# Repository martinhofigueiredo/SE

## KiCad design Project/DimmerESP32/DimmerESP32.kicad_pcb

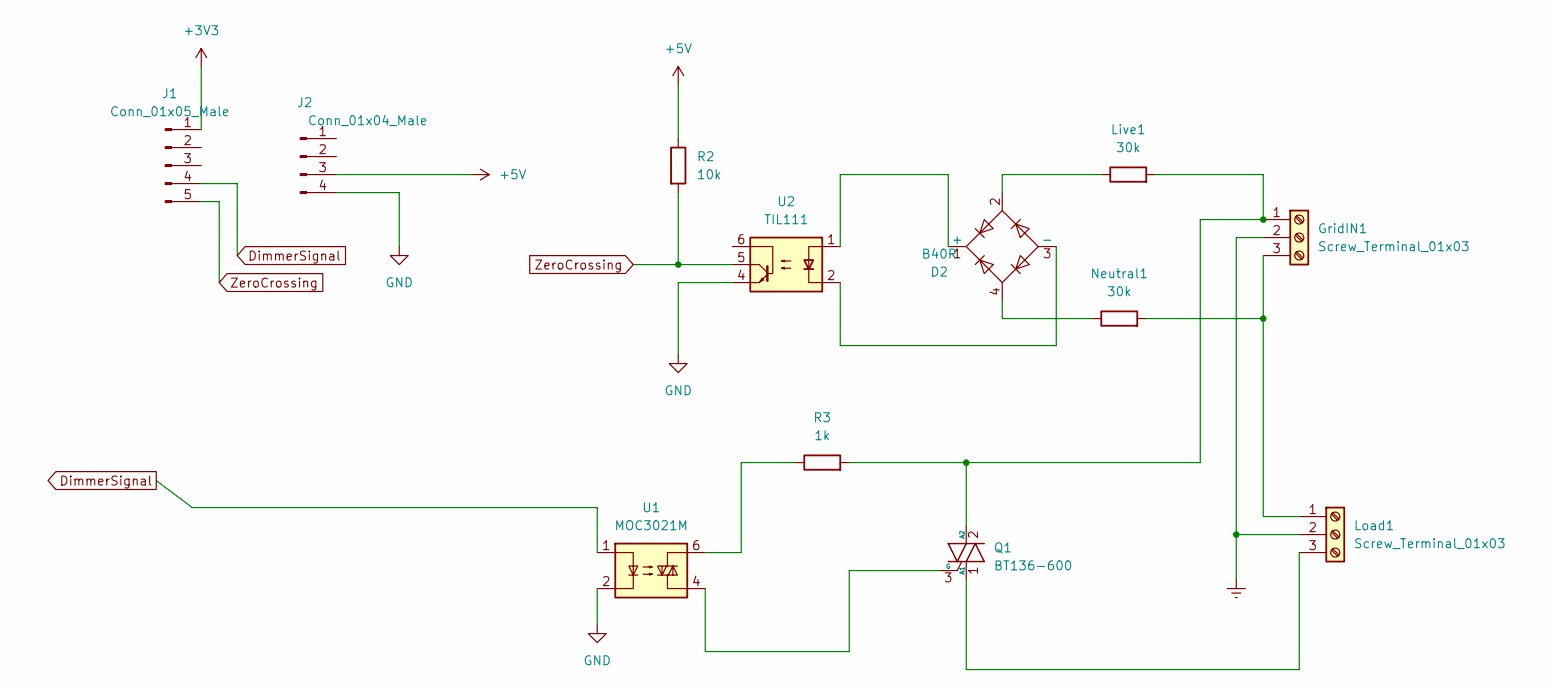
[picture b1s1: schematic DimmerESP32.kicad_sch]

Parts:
D2: B40R; Diode_Bridge_Round_D9.0mm
GridIN1: Screw_Terminal_01x03; TerminalBlock_Altech_AK300-3_P5.00mm
J1: Conn_01x05_Male; PinHeader_1x05_P2.54mm_Vertical
J2: Conn_01x04_Male; PinHeader_1x04_P2.54mm_Vertical
Live1: 30k; R_Axial_DIN0207_L6.3mm_D2.5mm_P10.16mm_Horizontal
Load1: Screw_Terminal_01x03; TerminalBlock_Altech_AK300-3_P5.00mm
Neutral1: 30k; R_Axial_DIN0207_L6.3mm_D2.5mm_P10.16mm_Horizontal
Q1: BT136-600; TO-220-3_Vertical
R2: 10k; R_Axial_DIN0207_L6.3mm_D2.5mm_P10.16mm_Horizontal
R3: 1k; R_Axial_DIN0207_L6.3mm_D2.5mm_P10.16mm_Horizontal
U1: MOC3021M; DIP-5-6_W7.62mm
U2: TIL111; DIP-6_W7.62mm

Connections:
+3V3: J1.1
+5V: J2.3, R2.1
DimmerSignal: J1.4, U1.1
Earth: GridIN1.2, Load1.2
GND: J2.4, U1.2, U2.4
unnamed: D2.1 (+), U2.1
unnamed: D2.2, Live1.1
unnamed: D2.3 (-), U2.2
unnamed: D2.4, Neutral1.1
unnamed: GridIN1.1, Live1.2, Q1.2 (A2), R3.2
unnamed: GridIN1.3, Load1.1, Neutral1.2
unnamed: Load1.3, Q1.1 (A1)
unnamed: Q1.3 (G), U1.4
unnamed: R3.1, U1.6
ZeroCrossing: J1.5, R2.2, U2.5

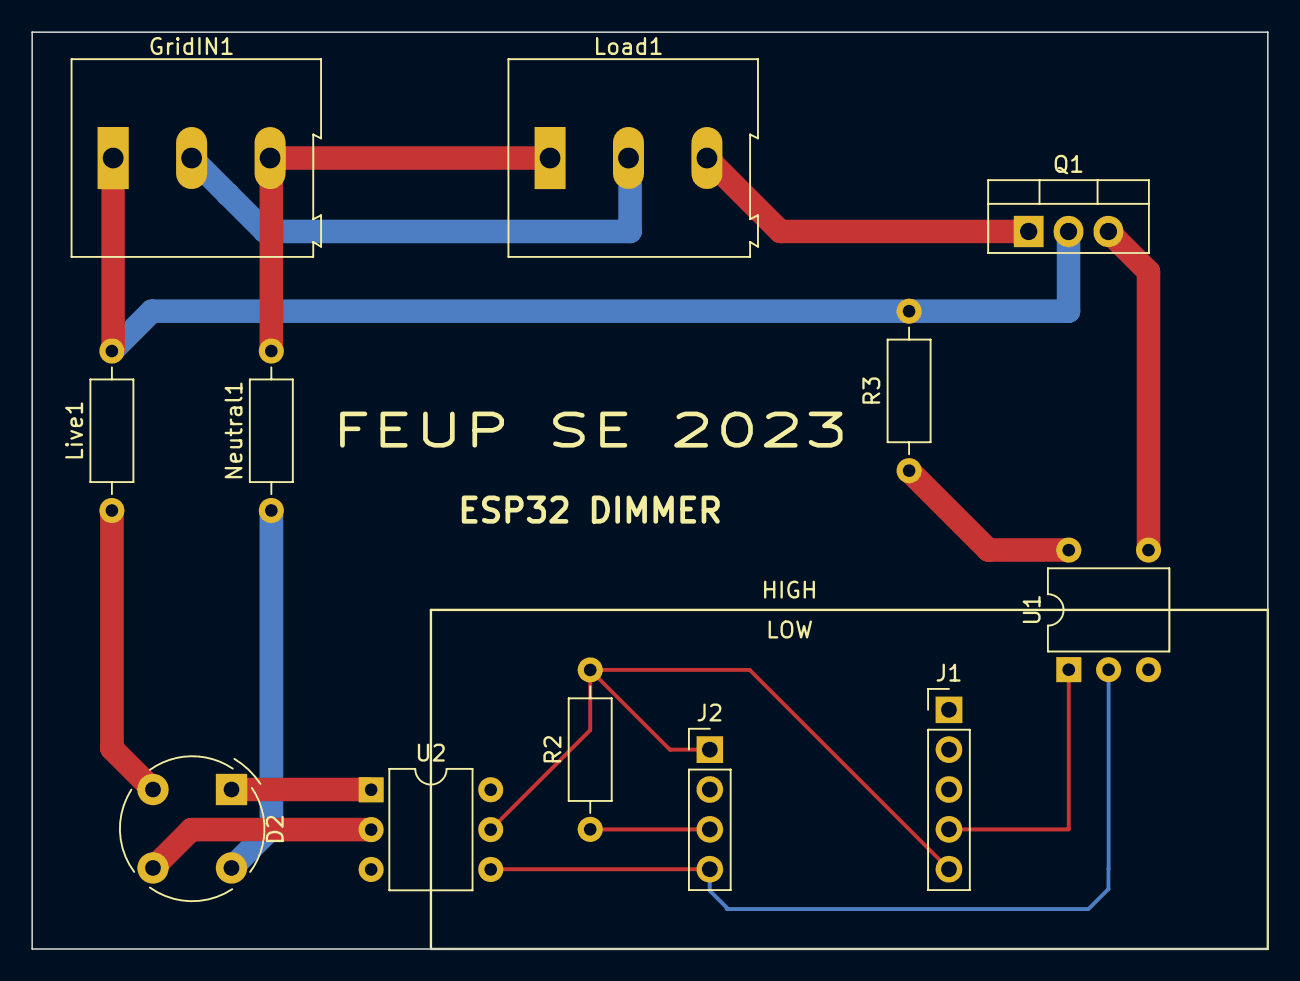
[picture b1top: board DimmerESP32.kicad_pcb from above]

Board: 2 copper layers, 78.7 x 58.4 mm, 12 parts (0 on the bottom side), 14 nets.

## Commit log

2022-09-27 read me
2022-09-28 Added readme and obsidian vault file
2022-10-18 Added gitpod button
2022-10-27 Remove Obsidian Folder
2022-10-27 added platformio configs
2022-10-27 stuff
2022-10-27 more stuff
2022-11-17 proprosal
2022-11-22 Finnessed this
2022-11-22 finessed 2
2022-11-22 fix link
2022-11-22 italicize
2022-12-20 First test on TTGO t-display only
2022-12-20 First test with tft library, a clock with NTP time
2022-12-26 pinout
2022-12-26 Weather cpp
2022-12-26 Todas as tasks separadas
    Segue o primeiro commit com todas as tasks testadas e a funcionar separadamente, agora basta unir tudo e ver se ainda corre...
2022-12-30 Game working in main.cpp
    We need to create a menu selection of the functions of the tasks
2022-12-30 Added Free rtos task for lora game
2022-12-30 Timing prototype based on timing api
2022-12-31 doing stuff
2022-12-31 Todas as tasks base criadas na main.cpp
2022-12-31 change pinned core tasks
2022-12-31 rough draft
2022-12-31 testing needed?
2022-12-31 task test idk
2023-01-02 add stuff
2023-01-13 paper and main ajustments
2023-01-14 Update v0 non functional
2023-01-14 Versão a funcionar sem o freeRtos
2023-01-15 Codigo dos jogos a funcionar e prints dos resultados temporais
2023-01-15 report
2023-01-15 Versão final
2023-01-15 Update com compilação dos games
2023-01-15 Todos prints de compilação e Serial.print()
2023-01-15 paper
2023-10-17 update for 2023/2024
2023-10-17 2023 version lets go
2023-10-18 added what was made in class
2023-10-19 2nd classe work and slide code
2023-10-24 hello hello
2023-10-24 added a bunch of pictures
2023-10-24 Added a bunch of stuffs
2023-10-24 exported pdf
2023-11-07 Project prep
2023-11-07 added wowki simulator
2023-11-07 add library IR
2023-11-07 With Sketch
2023-11-09 clean up
2023-11-09 Added Platformio Project
2023-11-09 Framwork Arduino
2023-11-09 Wokwi files added
2023-11-09 changes to C++ cause arduino
2023-11-09 everything in just not working
2023-11-09 Added gitpod dockerfile
2023-11-09 Reference Container
2023-11-21 Added project folder as home folder
2023-11-21 added stuffs
2023-11-23 Clean platformio out
2023-11-23 Compiling
2023-11-30 trying to fix the gitpod enviroment
2023-11-30 wifi and generating html "hello world"
2023-11-30 tested 2
2023-12-05 Functioning Simulator
2023-12-05 still doing and postbuild task
2023-12-05 test gpio driver
2023-12-05 Webpage slider and buttons semi-working
2023-12-05 Without build
2023-12-07 btn g41 for test
2023-12-07 No build folder, slider bug fixed
2023-12-07 fixed file stack
2023-12-07 OCD solved
2023-12-07 workinh and tested
2023-12-18 Webpage and delay update
2023-12-28 Schem and PCB
2023-12-28 Change 4N25 to TIL111
2024-01-08 Merged Wifi into main
2024-01-08 added stuff to gitignore
2024-01-08 Revert "Http Server over AP wifi mode"
2024-01-10 Updated KiCad
2024-01-10 Added Zero Crossing Stuff
2024-01-10 Add CMake source directory to VSCode settings
2024-01-11 Includes not working yet but i need sleep
2024-01-11 commit 2 electric bogallo
2024-01-11 This version functions 100%
2024-01-11 Remove LED and resistor from schem and PCB
2024-01-18 tiny fix
2024-01-18 tiny fix2
2024-01-19 with testes à trolha
2024-01-19 added performance monitor
2024-01-19 added defines
2024-01-19 change to prof
